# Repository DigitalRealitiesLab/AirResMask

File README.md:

# AirResMask

The repository contains building plans for the AirRes mask described in the following publication. Please cite this publication, if you build upon content of this repository:

Markus Tatzgern, Michael Domhardt, Martin Wolf, Michael Cenger, Gerlinde Emsenhuber, Radomir Dinic, Nathalie Gerner, and Arnulf Hartl. 2022. AirRes Mask: A Precise and Robust Virtual Reality Breathing Interface Utilizing Breathing Resistance as Output Modality. In CHI Conference on Human Factors in Computing Systems (CHI ’22), April 29-May 5, 2022, New Orleans, LA, USA. ACM, New York, NY, USA, https://doi.org/10.1145/3491102.3502090

The assembled mask:

Exploded view of mask showing components:

Example applications realized with mask:

This repository contains in the following folders:
- CAD: 3D models and printer files for custom parts of the mask
- Electronics: plans for custom electronics including a Bluetooth module
- Software: control software for the electronics and a Unity sample

Additional part list:
- Sensirion Mass Flow Meter [SFM3300](https://www.sensirion.com/en/flow-sensors/mass-flow-meters-for-high-precise-measurement-of-gases/proximal-flow-sensors-sfm3300-autoclavable-washable-or-single-use/) 
- [3M Respirator 6300](https://www.3m.com/3M/en_US/p/d/v000057396/)
- Servomotor SG90
- Power Bank with Micro USB connector

3rd party CAD files that could be interesting:
- [Servomotor SG90](https://grabcad.com/library/sg90-micro-servo-9g-tower-pro-1)
- Sensors: [SFM3300-D](https://www.sensirion.com/fileadmin/user_upload/customers/sensirion/Dokumente/5_Mass_Flow_Meters/Software/Sensirion_Mass_Flow_Meters_Software_SFM3300-D.step), [SFM3300-AW](https://www.sensirion.com/fileadmin/user_upload/customers/sensirion/Dokumente/5_Mass_Flow_Meters/Software/Sensirion_Mass_Flow_Meters_Software_SFM3300-D.step)

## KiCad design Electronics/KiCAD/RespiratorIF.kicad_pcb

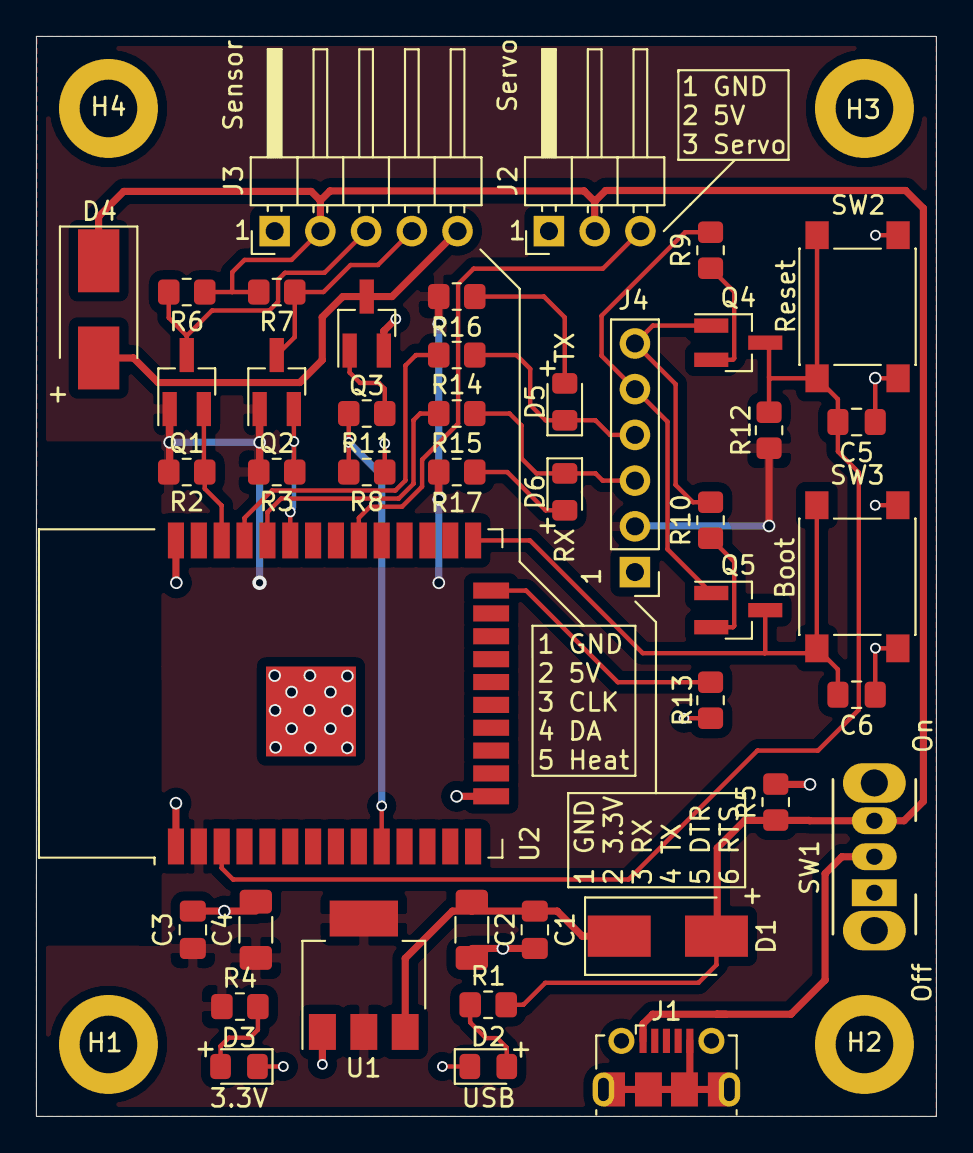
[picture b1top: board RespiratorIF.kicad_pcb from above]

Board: 2 copper layers, 50.0 x 60.0 mm, 47 parts (0 on the bottom side), 28 nets.

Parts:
C1, C3: 100nF; C_0805_2012Metric_Pad1.18x1.45mm_HandSolder
C2, C4: 47µF/10V; C_1206_3216Metric_Pad1.33x1.80mm_HandSolder
C5, C6: 1µF; C_0805_2012Metric_Pad1.18x1.45mm_HandSolder
D1, D4: SK24; D_SMB_Handsoldering
D2, D3: LED green; LED_0805_2012Metric_Pad1.15x1.40mm_HandSolder
D5, D6: LED yellow; LED_0805_2012Metric_Pad1.15x1.40mm_HandSolder
H1, H2, H3, H4: MountingHole; MountingHole_3.2mm_M3_ISO14580_Pad
J1: Power; USB_Micro-B_Molex-105017-0001
J2: Servo; PinHeader_1x03_P2.54mm_Horizontal
J3: Sensor; PinHeader_1x05_P2.54mm_Horizontal
J4: Program; PinHeader_1x06_P2.54mm_Vertical
Q1, Q2: BSS138; SOT-23_Handsoldering
Q3: AO3400A; SOT-23_Handsoldering
Q4, Q5: S8050; SOT-23_Handsoldering
R1: 4.7kΩ; R_0805_2012Metric_Pad1.20x1.40mm_HandSolder
R2, R3, R6, R7, R8, R9, R10, R12, R13: 10kΩ; R_0805_2012Metric_Pad1.20x1.40mm_HandSolder
R4, R16, R17: 1kΩ; R_0805_2012Metric_Pad1.20x1.40mm_HandSolder
R5: 20kΩ; R_0805_2012Metric_Pad1.20x1.40mm_HandSolder
R11: 100Ω; R_0805_2012Metric_Pad1.20x1.40mm_HandSolder
R14, R15: 470Ω; R_0805_2012Metric_Pad1.20x1.40mm_HandSolder
SW1: Off/On; SW_CuK_OS102011MA1QN1_SPDT_Angled
SW2: Reset; SW_Push_1P1T_NO_6x6mm_H9.5mm
SW3: Boot; SW_Push_1P1T_NO_6x6mm_H9.5mm
U1: AMS1117-3.3; SOT-223-3_TabPin2
U2: ESP32-WROOM-32

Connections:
+3V3: C3.1, C4.1, J4.2, Q1.1, Q2.1, R2.1, R3.1, R4.1, R12.1, R16.1, R17.1, U1.2, U2.2
+5V: D1.2, D4.1, J2.2, J3.2, R1.1, R5.1, R6.1, R7.1, SW1.3
/DTR: J4.5, Q5.1, R9.2
/EN: C5.1, Q4.3, R12.2, SW2.2, U2.3
/I2C_Clock_high: J3.3, Q1.3, R6.2
/I2C_Clock_low: Q1.2, R2.2, U2.36
/I2C_Data_high: J3.4, Q2.3, R7.2
/I2C_Data_low: Q2.2, R3.2, U2.33
/IO0: C6.1, Q5.3, SW3.2, U2.25
/RTS: J4.6, Q4.1, R10.2
/RX: D5.1, J4.4, R14.1
/Sensor_Heater: R8.1, R11.2, U2.10
/Sensor_Heater_GND: D4.2, J3.5, Q3.3
/Servo: J2.3, U2.30
/TX: D6.1, J4.3, R15.1
GND: C1.2, C2.2, C3.2, C4.2, C5.2, C6.2, D2.1, D3.1, J1.5, J1.6, J2.1, J3.1, J4.1, Q3.2, R5.2, R8.2, R13.2, SW2.1, SW3.1, U1.1, U2.1, U2.15, U2.38, U2.39
unnamed: C1.1, C2.1, D1.1, U1.3
unnamed: D2.2, R1.2
unnamed: D3.2, R4.2
unnamed: D5.2, R16.2
unnamed: D6.2, R17.2
unnamed: J1.1, SW1.2
unnamed: Q3.1, R11.1
unnamed: Q4.2, R9.1
unnamed: Q5.2, R10.1
unnamed: R13.1, U2.24
unnamed: R14.2, U2.35
unnamed: R15.2, U2.34

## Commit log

2021-11-24 Update LICENSE
    adjusted copyright holder information for license
2021-11-24 Add files via upload
    Initial commit of building material for AirResMask
2021-11-24 Add files via upload
    added example images
2021-11-24 Update README.md
    added images to readme
2021-11-24 Update README.md
    adjust image size
2021-11-29 added Unity example that shows how sensor values are received, applied and resistance settings are sent back to the mask
